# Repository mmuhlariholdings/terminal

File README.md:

<div align="center">

# Terminal 1

**A pocket Linux terminal with a real keyboard.**
Square 720 × 720 screen · BlackBerry Q20 keyboard and trackpad · Raspberry Pi CM4 · USB-C · carbon fibre back

[Website](https://mmuhlariholdings.github.io/terminal/) · [Product plan](system/plan/product-plan.md) · [3D model (Onshape)](https://cad.onshape.com/documents/8bfe7e43f7d7ec8135f9a829/w/29c38cad0998e4a6472b08e0/e/69201118ddf43601f28283ef) · [Contribute](CONTRIBUTING.md)

</div>

> [!IMPORTANT]
> **This project is vibe coded.** The plan, CAD, schematics, board layouts, firmware, Linux setup, docs and website are written
> largely by an AI coding assistant (Claude Code), directed and reviewed by humans. **Nothing has been built or tested on real
> hardware yet.** Treat every number as an estimate until a datasheet or a bench test confirms it. Items not yet verified are
> marked `CHECK` or *verify*. Checking them is one of the most useful contributions you can make. Why we work this way:
> [decision 0010](docs/decisions/0010-built-openly-with-an-ai-coding-assistant.md).

---

Terminal 1 does one job well: **working in a shell** on the go. SSH, `az login --use-device-code`, Claude Code, git, tmux,
everyday Linux. It boots straight into a full-screen terminal: no desktop, no browser, no notifications. Wi-Fi plus your
phone's hotspot covers connectivity.

It is a learning project first: KiCad, PCBs from JLCPCB and PCBWay, sourcing, 3D printing, carbon composites and Linux. We buy
proven modules where building them would teach little (the CM4 and the keyboard) and design our own boards around them.

## At a glance

| | |
|---|---|
| **Screen** | 4-inch 720 × 720 IPS, MIPI DSI: **90 × 45 characters** with an 8 × 16 font |
| **Keyboard** | BlackBerry Q20 replacement keyboard + trackpad; Ctrl / Esc / Tab / Fn above the keys; trackpad as arrow keys |
| **Computer** | Raspberry Pi Compute Module 4: 4 × Cortex-A72, 4 GB RAM, 32 GB eMMC, Wi-Fi 5, Bluetooth 5 |
| **Software** | Raspberry Pi OS Lite 64-bit · cage + foot · zsh · tmux · NetworkManager · Azure CLI · Node.js 22 · Claude Code |
| **Power** | 1S LiPo about 4,000–4,500 mAh, USB-C charging, runs while charging; about 4–6 h of terminal use (estimate) |
| **Size** | 84 × 150 × 19 mm, about 291 g (from the CAD model) |
| **Build** | Black aluminium mid-frame, carbon fibre back with a fibreglass radio window |
| **Our boards** | Keyboard and power board (RP2040, BQ25895, 5 V boost, MAX17048) · CM4 carrier board (4 layers, DSI, RTC) |

## Status

**Phase 0 (bench prototype) is next. First design pass done on 2026-11-16.**

| Area | State | Where |
|---|---|---|
| Plan | Converted to a living plan, decisions recorded | [`system/plan/`](system/plan/) · [`docs/decisions/`](docs/decisions/README.md) |
| 3D model | Full stack modelled in Onshape (FeatureScript), regenerates; fit check done | [`hardware/enclosure/`](hardware/enclosure/README.md) |
| Keyboard and power board | Pin map and circuit choices settled in the firmware; **schematic and layout not written yet** | [`hardware/keyboard-board/`](hardware/keyboard-board/README.md) |
| CM4 carrier board | Schematic ERC clean; layout DRC 0 violations; DSI and USB pairs still to route by hand | [`hardware/carrier-board/`](hardware/carrier-board/README.md) |
| Keyboard firmware | Written (Pico SDK + TinyUSB); host tests 5/5 pass; cross-compile runs in CI; not yet on hardware | [`firmware/keyboard-board/`](firmware/keyboard-board/README.md) |
| Linux | Installer, configs and status daemon written and unit tested; not yet run on a CM4 | [`linux/`](linux/README.md) |
| Website | Static launch page with the 3D model | [`website/`](website/README.md) |

## Roadmap

| Phase | What | Gate |
|---|---|---|
| **0 · Bench prototype** ← *we are here* | CM4 on its IO board, Q20 keyboard on a Pico, screen on the desk | SSH, `az login` and Claude Code from the bench keyboard |
| 1 · Keyboard and power board | Our RP2040 board from JLCPCB | Reliable typing, safe charging, clean shutdown from the power button |
| 2 · Carrier board | Our 4-layer CM4 carrier | Boots from the battery with screen and Wi-Fi |
| 3 · Enclosure | Printed shell → aluminium mid-frame → carbon back | Fits a jacket pocket, stays cool, Wi-Fi works with the back on |
| 4 · Daily driver | Battery tuning, disk encryption, key map refined | Two weeks without reaching for the laptop |
| 5 · Terminal 2 | Modem, bigger battery, optional CM5 | |

## Repository map

```
system/plan/          product-plan.md (the living plan) · interfaces.md (shared numbers) · the original PDF
docs/                 conventions.md · decisions/ (why things are the way they are) · media/ (renders)
hardware/enclosure/   terminal-1.fs (the Onshape model as code) · build sheet · .glb export
hardware/keyboard-board/   RP2040 keyboard and power board: generators, KiCad project, Gerbers, build sheet
hardware/carrier-board/    CM4 carrier: generators, KiCad project, routing notes, build sheet
firmware/keyboard-board/   RP2040 firmware (key map, trackpad, USB, power state machine) + host tests
linux/                install.sh, configs, terminal-1-statusd, pi-gen image stage
tools/                shared Python generators (KiCad schematic writer, board builder, checks)
website/              the launch page (static, GitHub Pages)
```

## Getting started

| You want to… | Start here |
|---|---|
| Understand the device | [Product plan](system/plan/product-plan.md), then [interfaces](system/plan/interfaces.md) |
| Look at the 3D model | [Onshape document](https://cad.onshape.com/documents/8bfe7e43f7d7ec8135f9a829/w/29c38cad0998e4a6472b08e0/e/69201118ddf43601f28283ef) and [`hardware/enclosure/`](hardware/enclosure/README.md) |
| Build the Phase 0 bench prototype | [`linux/README.md`](linux/README.md) and [`firmware/keyboard-board/README.md`](firmware/keyboard-board/) |
| Regenerate a schematic | `python3 hardware/<board>/electronics/generate_schematic.py --erc` (KiCad 10 installed) |
| Run the checks locally | `python3 tools/check_decisions.py` · `python3 -m unittest discover -s linux/status-daemon/tests` |
| Preview the website | `python3 -m http.server -d website/public 8000` → http://localhost:8000 |

Tools: git, Python 3, [KiCad 10](https://www.kicad.org/) (schematics, boards; its Python runs the board scripts), Java 21 (the
Freerouting autorouter), the [Pico SDK](https://github.com/raspberrypi/pico-sdk) and an Arm GCC toolchain (firmware), an
[Onshape](https://www.onshape.com/) account (free for public documents).

## Contributing

Everyone is welcome: electronics, CAD, firmware, Linux, docs, design, or simply **checking a datasheet against our files**.
Read [`CONTRIBUTING.md`](CONTRIBUTING.md), pick an issue labelled
[`good first issue`](https://github.com/mmuhlariholdings/terminal/labels/good%20first%20issue), and open a pull request.
Please follow the [Code of Conduct](CODE_OF_CONDUCT.md). Security issues: [`SECURITY.md`](SECURITY.md).

## Standing on shoulders

Beepy (SQFMI), Hackberry Pi, Solder Party's BBQ20KBD, ClockworkPi uConsole and MNT Pocket Reform showed the way; Raspberry Pi
publishes the CM4 IO board design we base our carrier on. Thank you.

## Licence

Hardware **CERN-OHL-S-2.0**, software **MIT**, documentation **CC BY-SA 4.0**. See [`LICENSE`](LICENSE). Terminal 1 is not
affiliated with Raspberry Pi Ltd or BlackBerry Ltd; their names are used only to describe the parts used.

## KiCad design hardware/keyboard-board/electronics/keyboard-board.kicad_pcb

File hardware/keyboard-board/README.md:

# Keyboard and power board

The 2-layer board behind the keyboard: RP2040 (keyboard, trackpad, USB device, power manager), BlackBerry Q20 keyboard and
trackpad connector, BQ25895 charger with power path, TPS61089 5.08 V boost for the CM4, MAX17048 gauge, USB-C, a TS3USB221
USB switch for service mode, power button, and the 24-way cable to the carrier board. 74 × 60 mm, Rev A.
Interfaces: [`system/plan/interfaces.md`](../../system/plan/interfaces.md) sections 3, 4, 6–8. Why: decisions 0004–0006.

## Status (2026-11-17)

STATUS_LINES

**Not ready to order.** The list of what must happen first is in [`build-sheet.md`](build-sheet.md) ("Before ordering").

## Where things are

| File | What |
|---|---|
| [`build-sheet.md`](build-sheet.md) | Design spec: inputs, outline, placement, parts and how sure each LCSC number is, checks, open items |
| [`electronics/generate_schematic.py`](electronics/generate_schematic.py) | The schematic, as a script (owns the RP2040 pin map) |
| [`electronics/parts.py`](electronics/parts.py) | LCSC numbers and footprints |
| [`electronics/pin-map.md`](electronics/pin-map.md) | RP2040 GPIOs, keyboard matrix, connector pinouts (generated) |
| [`electronics/netlist.md`](electronics/netlist.md) | Every net and part (generated) |
| [`electronics/circuit-notes.md`](electronics/circuit-notes.md) | Hand calculations: boost peak current, inductors, charger, LDO, battery life (estimates) |
| [`electronics/harness.md`](electronics/harness.md) | Cable and wires |
| [`electronics/generate_pcb.py`](electronics/generate_pcb.py) | The layout, as a script (placement, autorouting, DRC, renders, Gerbers, JLCPCB files) |
| `electronics/renders/`, `electronics/fabrication/` | Generated renders, Gerbers and JLCPCB BOM / placement files |
| [`../../firmware/keyboard-board/`](../../firmware/keyboard-board/) | The RP2040 firmware (its `src/board.h` must match `pin-map.md`; the schematic script checks it) |

## Rebuild

```sh
cd hardware/keyboard-board/electronics
python3 generate_schematic.py --erc        # schematic, net list, pin map, PDF; KiCad ERC must say 0 errors, 0 warnings
tools/fetch_tools.sh                       # once, from the repository root: Freerouting 2.0.1 (needs Java 21)
/Applications/KiCad/KiCad.app/Contents/Frameworks/Python.framework/Versions/3.9/bin/python3 generate_pcb.py --all
```

## Credits

The keyboard connector pinout, trackpad level shifting and matrix wiring follow Solder Party's
[BBQ20KBD](https://github.com/solderparty/bbq20kbd_hw) (CERN-OHL-1.2) and its firmware
[i2c_puppet](https://github.com/solderparty/i2c_puppet) (MIT). The RP2040 core circuit follows the Raspberry Pi Pico.

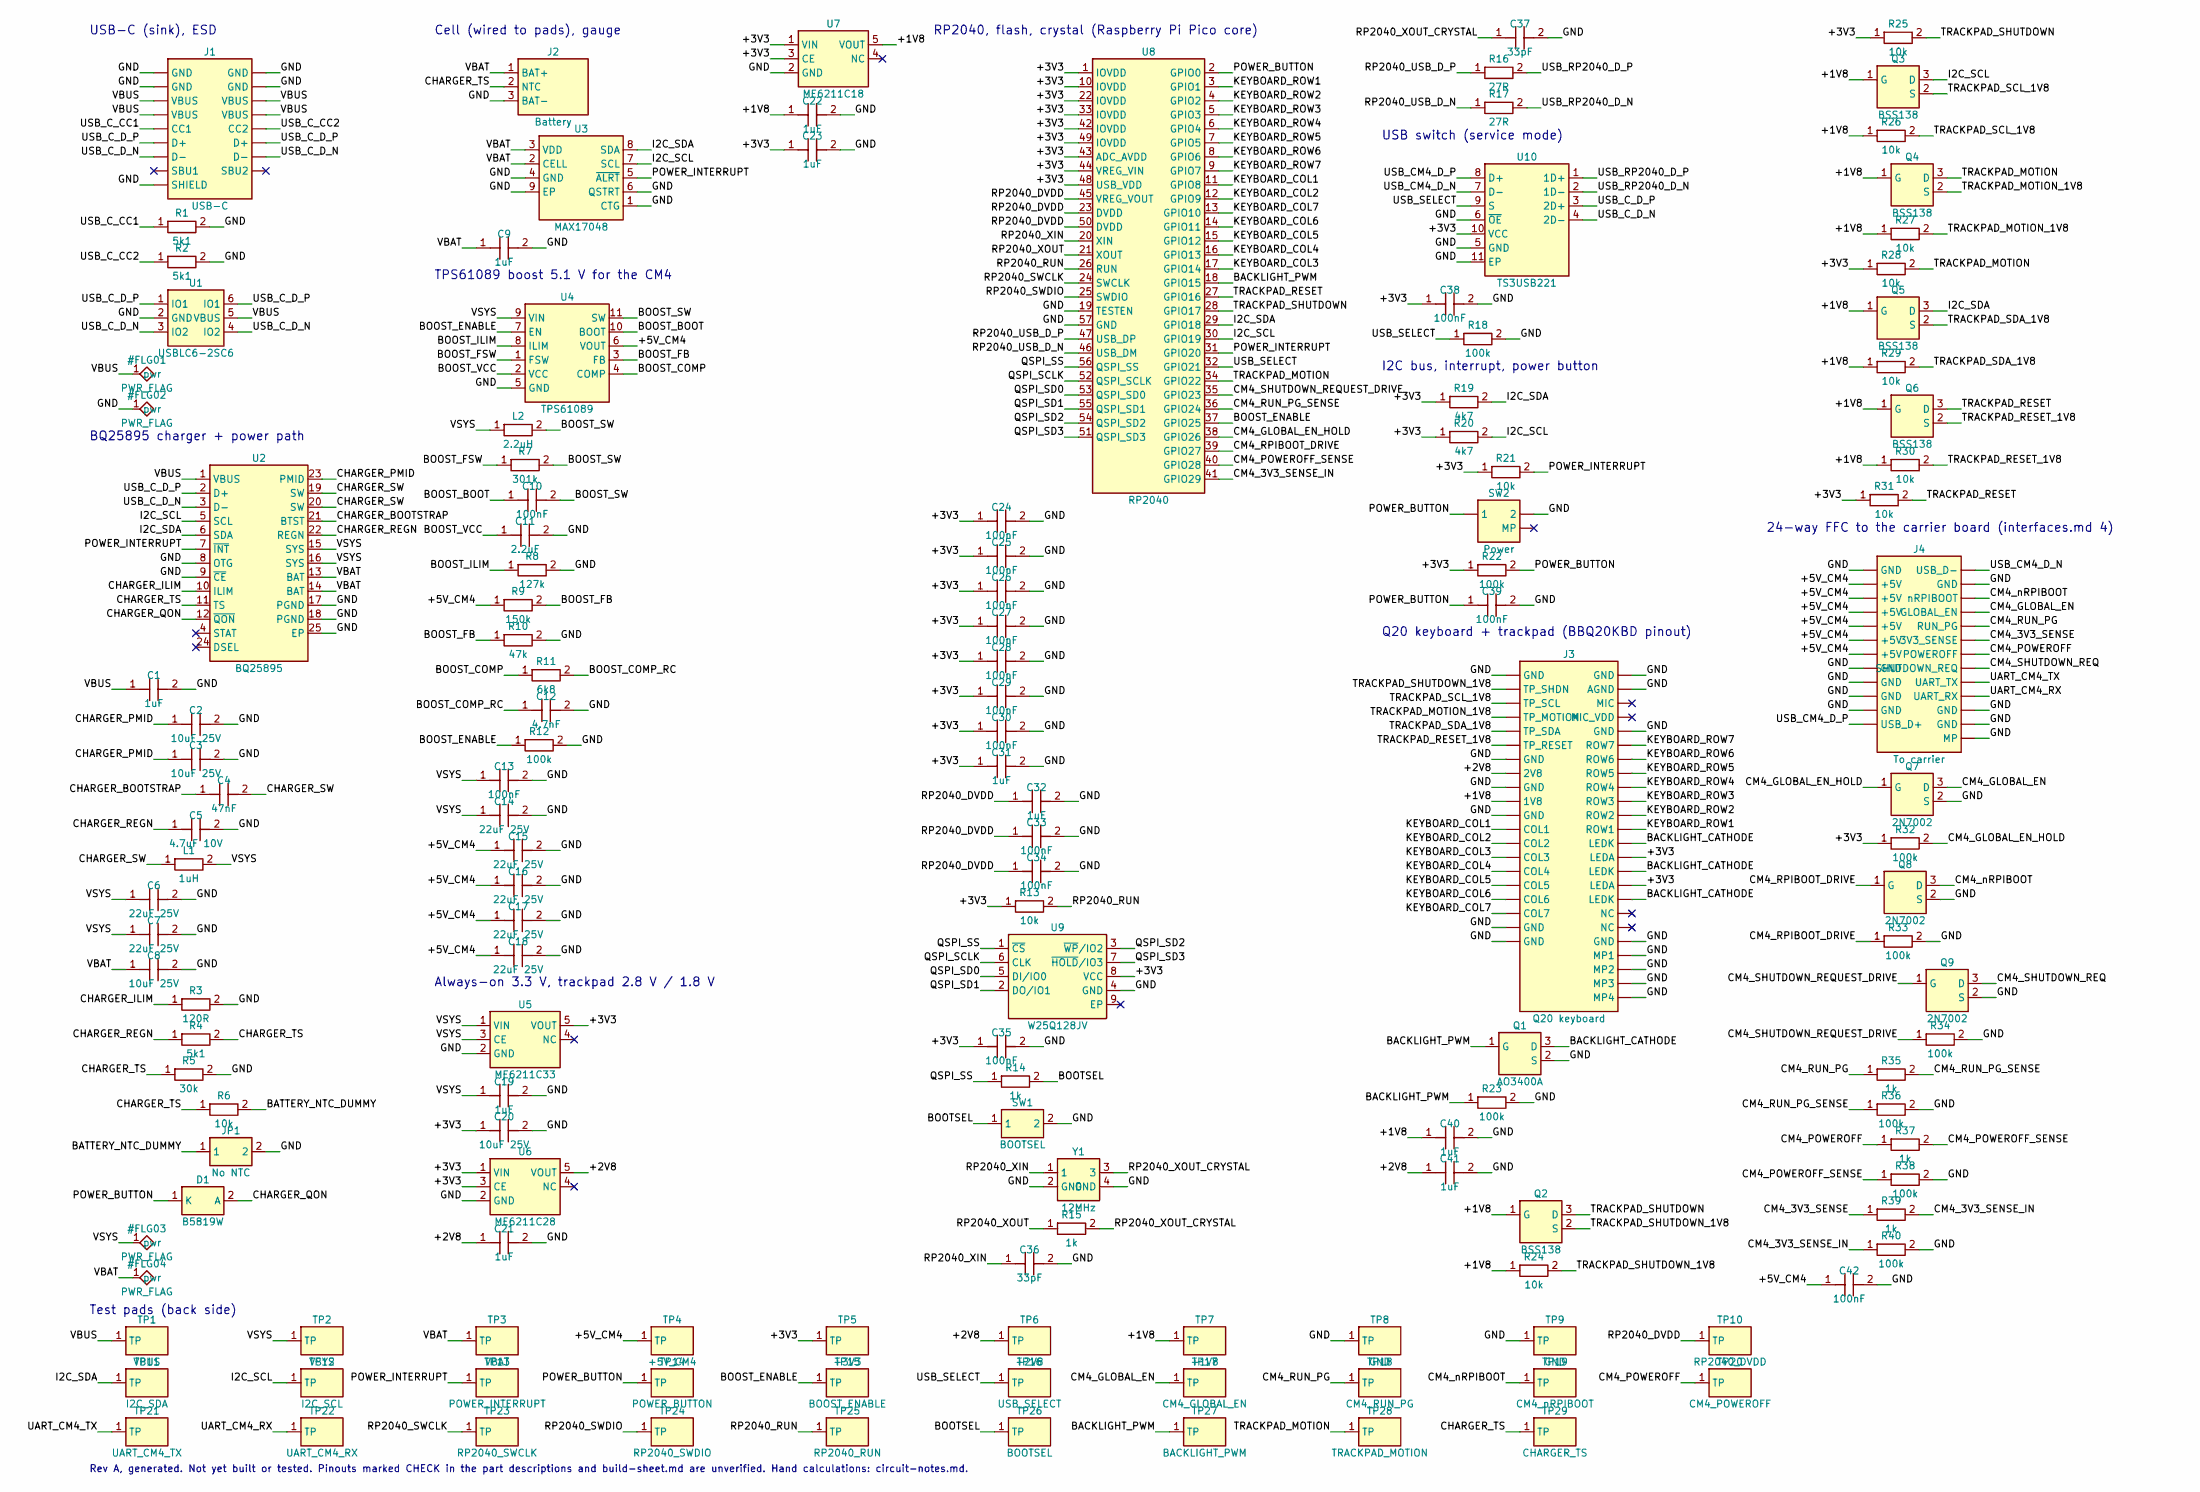
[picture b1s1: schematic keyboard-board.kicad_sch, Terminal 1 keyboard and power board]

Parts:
C1, C9, C19, C21, C22, C23, C31, C32, C40, C41: 1uF; C_0603_1608Metric; LCSC C15849
C2, C3, C8, C20: 10uF 25V; C_0805_2012Metric; LCSC C15850
C4: 47nF; C_0603_1608Metric
C5: 4.7uF 10V; C_0603_1608Metric
C6, C7, C14, C15, C16, C17, C18: 22uF 25V; C_1206_3216Metric; LCSC C12891
C10, C13, C24, C25, C26, C27, C28, C29, C30, C33, C34, C35, C38, C39, C42: 100nF; C_0603_1608Metric; LCSC C14663
C11: 2.2uF; C_0603_1608Metric
C12: 4.7nF; C_0603_1608Metric
C36, C37: 33pF; C_0603_1608Metric
D1: B5819W; D_SOD-123; LCSC C8598
J1: USB-C; USB_C_Receptacle_HRO_TYPE-C-31-M-12; LCSC C165948
J2: Battery; SolderWire-0.5sqmm_1x03_P4.6mm_D0.9mm_OD2.1mm
J3: Q20 keyboard; Hirose_BM20B-0.8-40DS-0.4V; LCSC C424543
J4: To carrier; Hirose_FH12-24S-0.5SH_1x24-1MP_P0.50mm_Horizontal; LCSC C202112
JP1: No NTC; SolderJumper-2_P1.3mm_Open_RoundedPad1.0x1.5mm
L1: 1uH; L_Changjiang_FXL0420; LCSC C167203
L2: 2.2uH; L_Changjiang_FXL0630; LCSC C167218
Q1: AO3400A; SOT-23; LCSC C20917
Q2, Q3, Q4, Q5, Q6: BSS138; SOT-23; LCSC C78284
Q7, Q8, Q9: 2N7002; SOT-23; LCSC C8545
R1, R2, R4: 5k1; R_0603_1608Metric; LCSC C23186
R3: 120R; R_0603_1608Metric
R5: 30k; R_0603_1608Metric
R6, R13, R21, R24, R25, R26, R27, R28, R29, R30, R31: 10k; R_0603_1608Metric; LCSC C25804
R7: 301k; R_0603_1608Metric
R8: 127k; R_0603_1608Metric
R9: 150k; R_0603_1608Metric
R10: 47k; R_0603_1608Metric
R11: 6k8; R_0603_1608Metric
R12, R18, R22, R23, R32, R33, R34, R36, R38, R40: 100k; R_0603_1608Metric; LCSC C25803
R14, R15, R35, R37, R39: 1k; R_0603_1608Metric; LCSC C21190
R16, R17: 27R; R_0603_1608Metric
R19, R20: 4k7; R_0603_1608Metric; LCSC C23162
SW1: BOOTSEL; SW_Push_1P1T_XKB_TS-1187A; LCSC C318884
SW2: Power; SW_Push_1P1T-MP_NO_Horizontal_Alps_SKRTLAE010; LCSC C110293
TP1: VBUS; TestPoint_Pad_D1.5mm
TP2: VSYS; TestPoint_Pad_D1.5mm
TP3: VBAT; TestPoint_Pad_D1.5mm
TP4: +5V_CM4; TestPoint_Pad_D1.5mm
TP5: +3V3; TestPoint_Pad_D1.5mm
TP6: +2V8; TestPoint_Pad_D1.5mm
TP7: +1V8; TestPoint_Pad_D1.5mm
TP8, TP9: GND; TestPoint_Pad_D1.5mm
TP10: RP2040_DVDD; TestPoint_Pad_D1.5mm
TP11: I2C_SDA; TestPoint_Pad_D1.5mm
TP12: I2C_SCL; TestPoint_Pad_D1.5mm
TP13: POWER_INTERRUPT; TestPoint_Pad_D1.5mm
TP14: POWER_BUTTON; TestPoint_Pad_D1.5mm
TP15: BOOST_ENABLE; TestPoint_Pad_D1.5mm
TP16: USB_SELECT; TestPoint_Pad_D1.5mm
TP17: CM4_GLOBAL_EN; TestPoint_Pad_D1.5mm
TP18: CM4_RUN_PG; TestPoint_Pad_D1.5mm
TP19: CM4_nRPIBOOT; TestPoint_Pad_D1.5mm
TP20: CM4_POWEROFF; TestPoint_Pad_D1.5mm
TP21: UART_CM4_TX; TestPoint_Pad_D1.5mm
TP22: UART_CM4_RX; TestPoint_Pad_D1.5mm
TP23: RP2040_SWCLK; TestPoint_Pad_D1.5mm
TP24: RP2040_SWDIO; TestPoint_Pad_D1.5mm
TP25: RP2040_RUN; TestPoint_Pad_D1.5mm
TP26: BOOTSEL; TestPoint_Pad_D1.5mm
TP27: BACKLIGHT_PWM; TestPoint_Pad_D1.5mm
TP28: TRACKPAD_MOTION; TestPoint_Pad_D1.5mm
TP29: CHARGER_TS; TestPoint_Pad_D1.5mm
U1: USBLC6-2SC6; SOT-23-6; LCSC C7519
U2: BQ25895; Texas_RTW_WQFN-24-1EP_4x4mm_P0.5mm_EP2.7x2.7mm; LCSC C80200
U3: MAX17048; TDFN-8-1EP_2x2mm_P0.5mm_EP0.8x1.2mm; LCSC C2682616
U4: TPS61089; Texas_VQFN-RNR0011A-11; LCSC C165129
U5: ME6211C33; SOT-23-5; LCSC C82942
U6: ME6211C28; SOT-23-5; LCSC C53099
U7: ME6211C18; SOT-23-5; LCSC C236671
U8: RP2040; QFN-56-1EP_7x7mm_P0.4mm_EP3.2x3.2mm; LCSC C2040
U9: W25Q128JV; WSON-8-1EP_6x5mm_P1.27mm_EP3.4x4.3mm; LCSC C190862
U10: TS3USB221; VSON-10-1EP_3x3mm_P0.5mm_EP1.65x2.4mm; LCSC C324071
Y1: 12MHz; Crystal_SMD_3225-4Pin_3.2x2.5mm; LCSC C9002

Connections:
/+1V8: C22.1, C40.1, J3.10 (1V8), Q2.1 (G), Q3.1 (G), Q4.1 (G), Q5.1 (G), Q6.1 (G), R24.1, R26.1, R27.1, R29.1, R30.1, TP7.1, U7.5 (VOUT)
/+2V8: C21.1, C41.1, J3.8 (2V8), TP6.1, U6.5 (VOUT)
/+3V3: C20.1, C23.1, C24.1, C25.1, C26.1, C27.1, C28.1, C29.1, C30.1, C31.1, C35.1, C38.1, J3.34 (LEDA), J3.36 (LEDA), R13.1, R19.1, R20.1, R21.1, R22.1, R25.1, R28.1, R31.1, R32.1, TP5.1, U5.5 (VOUT), U6.1 (VIN), U6.3 (CE), U7.1 (VIN), U7.3 (CE), U8.1 (IOVDD), U8.10 (IOVDD), U8.22 (IOVDD), U8.33 (IOVDD), U8.42 (IOVDD), U8.43 (ADC_AVDD), U8.44 (VREG_VIN), U8.48 (USB_VDD), U8.49 (IOVDD), U9.8 (VCC), U10.10 (VCC)
/+5V_CM4: C15.1, C16.1, C17.1, C18.1, C42.1, J4.2 (+5V), J4.3 (+5V), J4.4 (+5V), J4.5 (+5V), J4.6 (+5V), J4.7 (+5V), R9.1, TP4.1, U4.6 (VOUT)
/BACKLIGHT_CATHODE: J3.33 (LEDK), J3.35 (LEDK), J3.37 (LEDK), Q1.3 (D)
/BACKLIGHT_PWM: Q1.1 (G), R23.1, TP27.1, U8.18 (GPIO15)
/BATTERY_NTC_DUMMY: JP1.1, R6.2
/BOOST_BOOT: C10.1, U4.10 (BOOT)
/BOOST_COMP: R11.1, U4.4 (COMP)
/BOOST_COMP_RC: C12.1, R11.2
/BOOST_ENABLE: R12.1, TP15.1, U4.7 (EN), U8.37 (GPIO25)
/BOOST_FB: R9.2, R10.1, U4.3 (FB)
/BOOST_FSW: R7.1, U4.1 (FSW)
/BOOST_ILIM: R8.1, U4.8 (ILIM)
/BOOST_SW: C10.2, L2.2, R7.2, U4.11 (SW)
/BOOST_VCC: C11.1, U4.2 (VCC)
/BOOTSEL: R14.2, SW1.1, TP26.1
/CHARGER_BOOTSTRAP: C4.1, U2.21 (BTST)
/CHARGER_ILIM: R3.1, U2.10 (ILIM)
/CHARGER_PMID: C2.1, C3.1, U2.23 (PMID)
/CHARGER_QON: D1.2 (A), U2.12 (~QON)
/CHARGER_REGN: C5.1, R4.1, U2.22 (REGN)
/CHARGER_SW: C4.2, L1.1, U2.19 (SW), U2.20 (SW)
/CHARGER_TS: J2.2 (NTC), R4.2, R5.1, R6.1, TP29.1, U2.11 (TS)
/CM4_3V3_SENSE: J4.18 (3V3_SENSE), R39.1
/CM4_3V3_SENSE_IN: R39.2, R40.1, U8.41 (GPIO29)
/CM4_GLOBAL_EN: J4.16 (GLOBAL_EN), Q7.3 (D), TP17.1
/CM4_GLOBAL_EN_HOLD: Q7.1 (G), R32.2, U8.38 (GPIO26)
/CM4_POWEROFF: J4.19 (POWEROFF), R37.1, TP20.1
/CM4_POWEROFF_SENSE: R37.2, R38.1, U8.40 (GPIO28)
/CM4_RPIBOOT_DRIVE: Q8.1 (G), R33.1, U8.39 (GPIO27)
/CM4_RUN_PG: J4.17 (RUN_PG), R35.1, TP18.1
/CM4_RUN_PG_SENSE: R35.2, R36.1, U8.36 (GPIO24)
/CM4_SHUTDOWN_REQ: J4.20 (SHUTDOWN_REQ), Q9.3 (D)
/CM4_SHUTDOWN_REQUEST_DRIVE: Q9.1 (G), R34.1, U8.35 (GPIO23)
/CM4_nRPIBOOT: J4.15 (nRPIBOOT), Q8.3 (D), TP19.1
/GND: C1.2, C2.2, C3.2, C5.2, C6.2, C7.2, C8.2, C9.2, C11.2, C12.2, C13.2, C14.2, C15.2, C16.2, C17.2, C18.2, C19.2, C20.2, C21.2, C22.2, C23.2, C24.2, C25.2, C26.2, C27.2, C28.2, C29.2, C30.2, C31.2, C32.2, C33.2, C34.2, C35.2, C36.2, C37.2, C38.2, C39.2, C40.2, C41.2, C42.2, J1.A1 (GND), J1.A12 (GND), J1.B1 (GND), J1.B12 (GND), J1.SH (SHIELD), J2.3 (BAT-), J3.1 (GND), J3.7 (GND), J3.9 (GND), J3.11 (GND), J3.19 (GND), J3.20 (GND), J3.21 (GND), J3.22 (AGND), J3.25 (GND), J3.40 (GND), J3.MP1, J3.MP2, J3.MP3, J3.MP4, J4.1 (GND), J4.8 (GND), J4.9 (GND), J4.10 (GND), J4.11 (GND), J4.14 (GND), J4.23 (GND), J4.24 (GND), J4.MP, JP1.2, Q1.2 (S), Q7.2 (S), Q8.2 (S), Q9.2 (S), R1.2, R2.2, R3.2, R5.2, R8.2, R10.2, R12.2, R18.2, R23.2, R33.2, R34.2, R36.2, R38.2, R40.2, SW1.2, SW2.2, TP8.1, TP9.1, U1.2 (GND), U2.8 (OTG), U2.9 (~CE), U2.17 (PGND), U2.18 (PGND), U2.25 (EP), U3.1 (CTG), U3.4 (GND), U3.6 (QSTRT), U3.9 (EP), U4.5 (GND), U5.2 (GND), U6.2 (GND), U7.2 (GND), U8.19 (TESTEN), U8.57 (GND), U9.4 (GND), U10.5 (GND), U10.6 (~OE), U10.11 (EP), Y1.2 (GND), Y1.4 (GND)
/I2C_SCL: Q3.3 (D), R20.2, TP12.1, U2.5 (SCL), U3.7 (SCL), U8.30 (GPIO19)
/I2C_SDA: Q5.3 (D), R19.2, TP11.1, U2.6 (SDA), U3.8 (SDA), U8.29 (GPIO18)
/KEYBOARD_COL1: J3.12 (COL1), U8.11 (GPIO8)
/KEYBOARD_COL2: J3.13 (COL2), U8.12 (GPIO9)
/KEYBOARD_COL3: J3.14 (COL3), U8.17 (GPIO14)
/KEYBOARD_COL4: J3.15 (COL4), U8.16 (GPIO13)
/KEYBOARD_COL5: J3.16 (COL5), U8.15 (GPIO12)
/KEYBOARD_COL6: J3.17 (COL6), U8.14 (GPIO11)
/KEYBOARD_COL7: J3.18 (COL7), U8.13 (GPIO10)
/KEYBOARD_ROW1: J3.32 (ROW1), U8.3 (GPIO1)
/KEYBOARD_ROW2: J3.31 (ROW2), U8.4 (GPIO2)
/KEYBOARD_ROW3: J3.30 (ROW3), U8.5 (GPIO3)
/KEYBOARD_ROW4: J3.29 (ROW4), U8.6 (GPIO4)
/KEYBOARD_ROW5: J3.28 (ROW5), U8.7 (GPIO5)
/KEYBOARD_ROW6: J3.27 (ROW6), U8.8 (GPIO6)
/KEYBOARD_ROW7: J3.26 (ROW7), U8.9 (GPIO7)
/POWER_BUTTON: C39.1, D1.1 (K), R22.2, SW2.1, TP14.1, U8.2 (GPIO0)
/POWER_INTERRUPT: R21.2, TP13.1, U2.7 (~INT), U3.5 (~ALRT), U8.31 (GPIO20)
/QSPI_SCLK: U8.52 (QSPI_SCLK), U9.6 (CLK)
/QSPI_SD0: U8.53 (QSPI_SD0), U9.5 (DI/IO0)
/QSPI_SD1: U8.55 (QSPI_SD1), U9.2 (DO/IO1)
/QSPI_SD2: U8.54 (QSPI_SD2), U9.3 (~WP/IO2)
/QSPI_SD3: U8.51 (QSPI_SD3), U9.7 (~HOLD/IO3)
/QSPI_SS: R14.1, U8.56 (QSPI_SS), U9.1 (~CS)
/RP2040_DVDD: C32.1, C33.1, C34.1, TP10.1, U8.23 (DVDD), U8.45 (VREG_VOUT), U8.50 (DVDD)
/RP2040_RUN: R13.2, TP25.1, U8.26 (RUN)
/RP2040_SWCLK: TP23.1, U8.24 (SWCLK)
/RP2040_SWDIO: TP24.1, U8.25 (SWDIO)
/RP2040_USB_D_N: R17.1, U8.46 (USB_DM)
/RP2040_USB_D_P: R16.1, U8.47 (USB_DP)
/RP2040_XIN: C36.1, U8.20 (XIN), Y1.1
/RP2040_XOUT: R15.1, U8.21 (XOUT)
/RP2040_XOUT_CRYSTAL: C37.1, R15.2, Y1.3
/TRACKPAD_MOTION: Q4.3 (D), R28.2, TP28.1, U8.34 (GPIO22)
/TRACKPAD_MOTION_1V8: J3.4 (TP_MOTION), Q4.2 (S), R27.2
/TRACKPAD_RESET: Q6.3 (D), R31.2, U8.27 (GPIO16)
/TRACKPAD_RESET_1V8: J3.6 (TP_RESET), Q6.2 (S), R30.2
/TRACKPAD_SCL_1V8: J3.3 (TP_SCL), Q3.2 (S), R26.2
/TRACKPAD_SDA_1V8: J3.5 (TP_SDA), Q5.2 (S), R29.2
/TRACKPAD_SHUTDOWN: Q2.3 (D), R25.2, U8.28 (GPIO17)
/TRACKPAD_SHUTDOWN_1V8: J3.2 (TP_SHDN), Q2.2 (S), R24.2
/UART_CM4_RX: J4.22 (UART_RX), TP22.1
/UART_CM4_TX: J4.21 (UART_TX), TP21.1
/USB_CM4_D_N: J4.13 (USB_D-), U10.7 (D-)
/USB_CM4_D_P: J4.12 (USB_D+), U10.8 (D+)
/USB_C_CC1: J1.A5 (CC1), R1.1
/USB_C_CC2: J1.B5 (CC2), R2.1
/USB_C_D_N: J1.A7 (D-), J1.B7 (D-), U1.3 (IO2), U1.4 (IO2), U2.3 (D-), U10.4 (2D-)
/USB_C_D_P: J1.A6 (D+), J1.B6 (D+), U1.1 (IO1), U1.6 (IO1), U2.2 (D+), U10.3 (2D+)
/USB_RP2040_D_N: R17.2, U10.2 (1D-)
/USB_RP2040_D_P: R16.2, U10.1 (1D+)
/USB_SELECT: R18.1, TP16.1, U8.32 (GPIO21), U10.9 (S)
/VBAT: C8.1, C9.1, J2.1 (BAT+), TP3.1, U2.13 (BAT), U2.14 (BAT), U3.2 (CELL), U3.3 (VDD)
/VBUS: C1.1, J1.A4 (VBUS), J1.A9 (VBUS), J1.B4 (VBUS), J1.B9 (VBUS), TP1.1, U1.5 (VBUS), U2.1 (VBUS)
/VSYS: C6.1, C7.1, C13.1, C14.1, C19.1, L1.2, L2.1, TP2.1, U2.15 (SYS), U2.16 (SYS), U4.9 (VIN), U5.1 (VIN), U5.3 (CE)

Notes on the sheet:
USB-C (sink), ESD
BQ25895 charger + power path
Cell (wired to pads), gauge
TPS61089 boost 5.1 V for the CM4
Always-on 3.3 V, trackpad 2.8 V / 1.8 V
RP2040, flash, crystal (Raspberry Pi Pico core)
USB switch (service mode)
I2C bus, interrupt, power button
Q20 keyboard + trackpad (BBQ20KBD pinout)
24-way FFC to the carrier board (interfaces.md 4)
Test pads (back side)
Rev A, generated. Not yet built or tested. Pinouts marked CHECK in the part descriptions and build-sheet.md are unverified. Hand calculations: circuit-notes.md.

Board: 2 copper layers, 145 parts (140 on the bottom side), 92 nets, no tracks yet.

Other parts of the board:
H1, H2, H3, H4: M2; MountingHole_2.2mm_M2

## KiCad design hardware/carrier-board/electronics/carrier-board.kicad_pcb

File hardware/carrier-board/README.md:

# CM4 carrier board

The 4-layer board behind the screen: Raspberry Pi CM4 on two Hirose DF40 connectors, the 22-pin DSI display connector (Pi
standard, as the CM4 IO board's DISP1), a PCF85063A real-time clock with a CR2032, status LEDs, serial console pads, and the
24-way cable to the keyboard board. 74 × 72 mm, Rev A. Design spec: [`build-sheet.md`](build-sheet.md).

## Status (2026-11-17)

| Check | Result |
|---|---|
| Schematic | Generated; **KiCad ERC 0 errors, 0 warnings** (32 parts, 45 nets); all 200 CM4 pins accounted for in [`electronics/pin-map.md`](electronics/pin-map.md) |
| Layout | Placed and autorouted except the high-speed pairs; **DRC 0 violations, 16 unconnected pads** (DSI1: 10, USB: 6) |
| Ready to order? | **No.** The DSI and USB pairs must be routed by hand: [`electronics/routing-notes.md`](electronics/routing-notes.md). Gerbers are in `electronics/fabrication/` marked **not for order** |
| Impedance | Estimated widths for JLCPCB JLC04161H-7628 in [`electronics/circuit-notes.md`](electronics/circuit-notes.md); confirm with JLCPCB's calculator |

## Regenerate

```sh
cd hardware/carrier-board/electronics
python3 generate_schematic.py --erc                     # schematic, ERC, PDF, netlist.md, pin-map.md
tools/fetch_tools.sh                                    # once, from the repository root: Freerouting
/Applications/KiCad/KiCad.app/Contents/Frameworks/Python.framework/Versions/3.9/bin/python3 generate_pcb.py --all
```

`generate_pcb.py` checks each of the CM4's 200 pads against the CM4 IO board footprint geometry and stops if any is off by more
than 0.01 mm. Its four-layer helpers are in `board_four_layer.py`; `estimate_impedance.py` reproduces the impedance table.

## Credits

Based on Raspberry Pi's CM4 IO board design (CM4IOv5): RTC circuit, status LEDs, DISP1 pinout and CM4 footprint geometry.
Raspberry Pi publishes those files for reuse in customers' designs; check their current terms before redistributing copies.

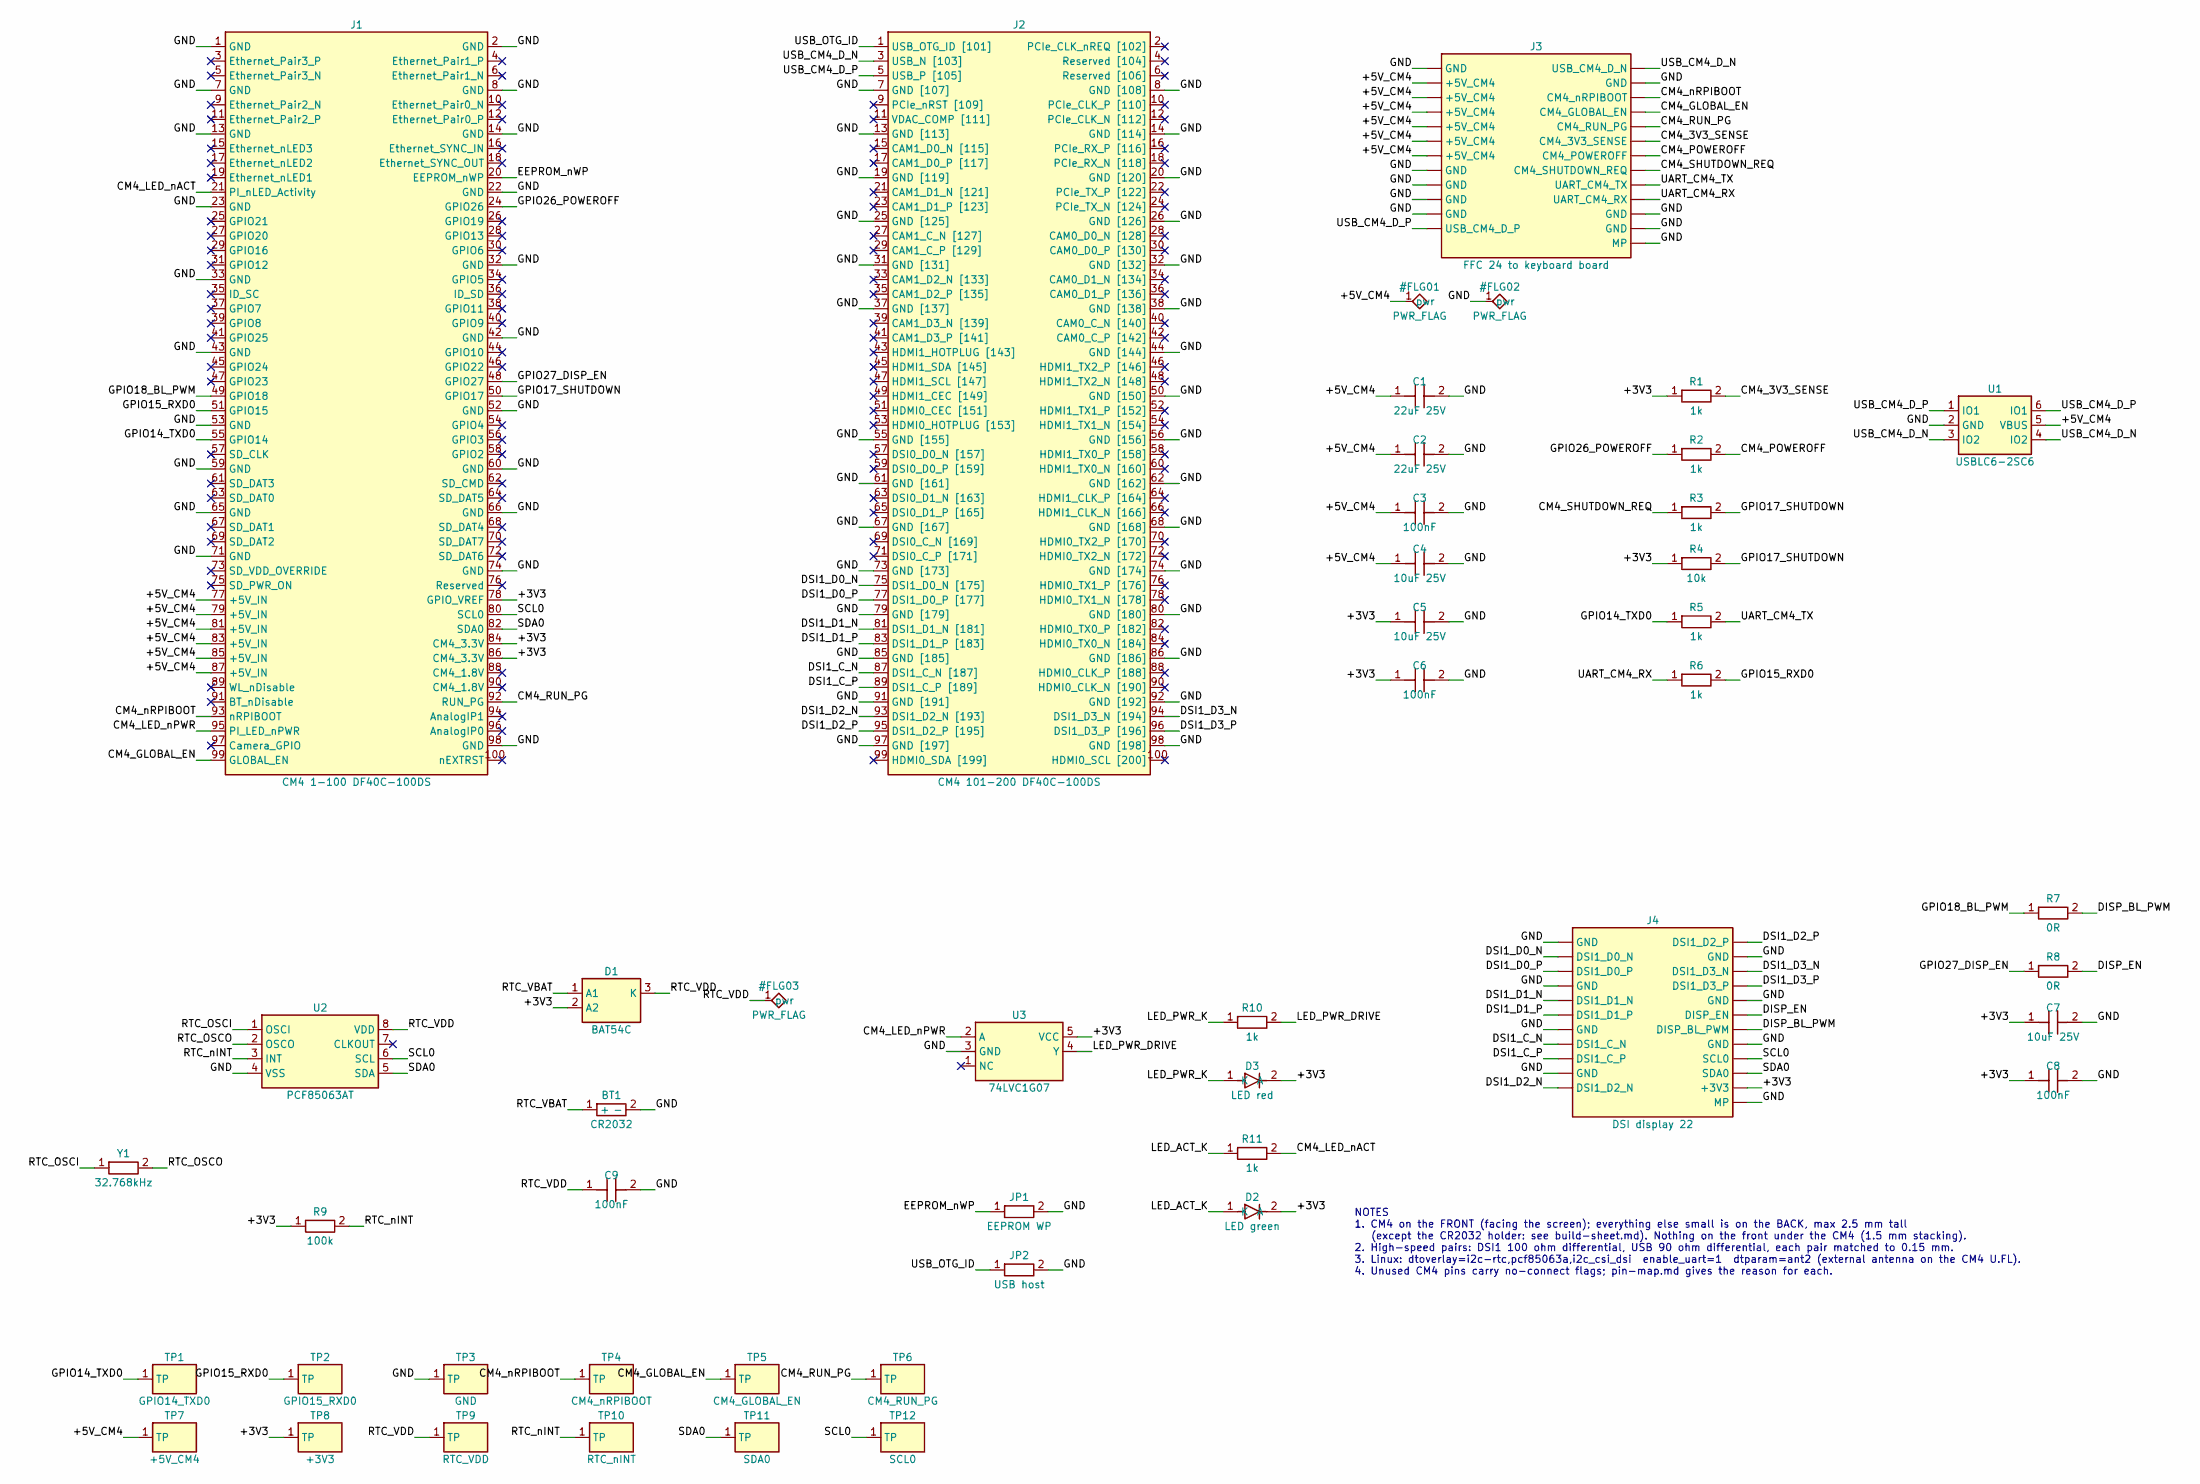
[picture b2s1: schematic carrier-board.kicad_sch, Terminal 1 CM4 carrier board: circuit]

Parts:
BT1: CR2032; BatteryHolder_Keystone_3034_1x20mm; LCSC CHECK
C1, C2: 22uF 25V; C_1206_3216Metric; LCSC C12891
C3, C6, C8, C9: 100nF; C_0603_1608Metric; LCSC C14663
C4, C5, C7: 10uF 25V; C_0805_2012Metric; LCSC C15850
D1: BAT54C; SOT-23; LCSC CHECK
D2: LED green; LED_0603_1608Metric; LCSC C72043
D3: LED red; LED_0603_1608Metric; LCSC C2286
J1: CM4 1-100 DF40C-100DS; Hirose_DF40C-100DS-0.4V_2x50_P0.4mm; LCSC CHECK
J2: CM4 101-200 DF40C-100DS; Hirose_DF40C-100DS-0.4V_2x50_P0.4mm; LCSC CHECK
J3: FFC 24 to keyboard board; Hirose_FH12-24S-0.5SH_1x24-1MP_P0.50mm_Horizontal; LCSC CHECK
J4: DSI display 22; Hirose_FH12-22S-0.5SH_1x22-1MP_P0.50mm_Horizontal; LCSC CHECK
JP1: EEPROM WP; SolderJumper-2_P1.3mm_Open_RoundedPad1.0x1.5mm
JP2: USB host; SolderJumper-2_P1.3mm_Open_RoundedPad1.0x1.5mm
R1, R2, R3, R5, R6, R10, R11: 1k; R_0603_1608Metric; LCSC C21190
R4: 10k; R_0603_1608Metric; LCSC C25804
R7, R8: 0R; R_0603_1608Metric; LCSC C21189
R9: 100k; R_0603_1608Metric; LCSC C25803
TP1: GPIO14_TXD0; TestPoint_Pad_D1.5mm
TP2: GPIO15_RXD0; TestPoint_Pad_D1.5mm
TP3: GND; TestPoint_Pad_D1.5mm
TP4: CM4_nRPIBOOT; TestPoint_Pad_D1.5mm
TP5: CM4_GLOBAL_EN; TestPoint_Pad_D1.5mm
TP6: CM4_RUN_PG; TestPoint_Pad_D1.5mm
TP7: +5V_CM4; TestPoint_Pad_D1.5mm
TP8: +3V3; TestPoint_Pad_D1.5mm
TP9: RTC_VDD; TestPoint_Pad_D1.5mm
TP10: RTC_nINT; TestPoint_Pad_D1.5mm
TP11: SDA0; TestPoint_Pad_D1.5mm
TP12: SCL0; TestPoint_Pad_D1.5mm
U1: USBLC6-2SC6; SOT-23-6; LCSC C7519
U2: PCF85063AT; SOIC-8_3.9x4.9mm_P1.27mm; LCSC CHECK
U3: 74LVC1G07; SOT-353_SC-70-5; LCSC CHECK
Y1: 32.768kHz; Crystal_SMD_3215-2Pin_3.2x1.5mm; LCSC CHECK

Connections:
/+3V3: C5.1, C6.1, C7.1, C8.1, D1.2 (A2), D2.2 (A), D3.2 (A), J1.78 (GPIO_VREF), J1.84 (CM4_3.3V), J1.86 (CM4_3.3V), J4.22 (+3V3), R1.1, R4.1, R9.1, TP8.1, U3.5 (VCC)
/+5V_CM4: C1.1, C2.1, C3.1, C4.1, J1.77 (+5V_IN), J1.79 (+5V_IN), J1.81 (+5V_IN), J1.83 (+5V_IN), J1.85 (+5V_IN), J1.87 (+5V_IN), J3.2 (+5V_CM4), J3.3 (+5V_CM4), J3.4 (+5V_CM4), J3.5 (+5V_CM4), J3.6 (+5V_CM4), J3.7 (+5V_CM4), TP7.1, U1.5 (VBUS)
/CM4_3V3_SENSE: J3.18 (CM4_3V3_SENSE), R1.2
/CM4_GLOBAL_EN: J1.99 (GLOBAL_EN), J3.16 (CM4_GLOBAL_EN), TP5.1
/CM4_LED_nACT: J1.21 (PI_nLED_Activity), R11.2
/CM4_LED_nPWR: J1.95 (PI_LED_nPWR), U3.2 (A)
/CM4_POWEROFF: J3.19 (CM4_POWEROFF), R2.2
/CM4_RUN_PG: J1.92 (RUN_PG), J3.17 (CM4_RUN_PG), TP6.1
/CM4_SHUTDOWN_REQ: J3.20 (CM4_SHUTDOWN_REQ), R3.1
/CM4_nRPIBOOT: J1.93 (nRPIBOOT), J3.15 (CM4_nRPIBOOT), TP4.1
/DISP_BL_PWM: J4.18 (DISP_BL_PWM), R7.2
/DISP_EN: J4.17 (DISP_EN), R8.2
/DSI1_C_N: J2.87 (DSI1_C_N [187]), J4.8 (DSI1_C_N)
/DSI1_C_P: J2.89 (DSI1_C_P [189]), J4.9 (DSI1_C_P)
/DSI1_D0_N: J2.75 (DSI1_D0_N [175]), J4.2 (DSI1_D0_N)
/DSI1_D0_P: J2.77 (DSI1_D0_P [177]), J4.3 (DSI1_D0_P)
/DSI1_D1_N: J2.81 (DSI1_D1_N [181]), J4.5 (DSI1_D1_N)
/DSI1_D1_P: J2.83 (DSI1_D1_P [183]), J4.6 (DSI1_D1_P)
/DSI1_D2_N: J2.93 (DSI1_D2_N [193]), J4.11 (DSI1_D2_N)
/DSI1_D2_P: J2.95 (DSI1_D2_P [195]), J4.12 (DSI1_D2_P)
/DSI1_D3_N: J2.94 (DSI1_D3_N [194]), J4.14 (DSI1_D3_N)
/DSI1_D3_P: J2.96 (DSI1_D3_P [196]), J4.15 (DSI1_D3_P)
/EEPROM_nWP: J1.20 (EEPROM_nWP), JP1.1
/GND: BT1.2 (-), C1.2, C2.2, C3.2, C4.2, C5.2, C6.2, C7.2, C8.2, C9.2, J1.1 (GND), J1.2 (GND), J1.7 (GND), J1.8 (GND), J1.13 (GND), J1.14 (GND), J1.22 (GND), J1.23 (GND), J1.32 (GND), J1.33 (GND), J1.42 (GND), J1.43 (GND), J1.52 (GND), J1.53 (GND), J1.59 (GND), J1.60 (GND), J1.65 (GND), J1.66 (GND), J1.71 (GND), J1.74 (GND), J1.98 (GND), J2.7 (GND [107]), J2.8 (GND [108]), J2.13 (GND [113]), J2.14 (GND [114]), J2.19 (GND [119]), J2.20 (GND [120]), J2.25 (GND [125]), J2.26 (GND [126]), J2.31 (GND [131]), J2.32 (GND [132]), J2.37 (GND [137]), J2.38 (GND [138]), J2.44 (GND [144]), J2.50 (GND [150]), J2.55 (GND [155]), J2.56 (GND [156]), J2.61 (GND [161]), J2.62 (GND [162]), J2.67 (GND [167]), J2.68 (GND [168]), J2.73 (GND [173]), J2.74 (GND [174]), J2.79 (GND [179]), J2.80 (GND [180]), J2.85 (GND [185]), J2.86 (GND [186]), J2.91 (GND [191]), J2.92 (GND [192]), J2.97 (GND [197]), J2.98 (GND [198]), J3.1 (GND), J3.8 (GND), J3.9 (GND), J3.10 (GND), J3.11 (GND), J3.14 (GND), J3.23 (GND), J3.24 (GND), J3.MP, J4.1 (GND), J4.4 (GND), J4.7 (GND), J4.10 (GND), J4.13 (GND), J4.16 (GND), J4.19 (GND), J4.MP, JP1.2, JP2.2, TP3.1, U1.2 (GND), U2.4 (VSS), U3.3 (GND)
/GPIO14_TXD0: J1.55 (GPIO14), R5.1, TP1.1
/GPIO15_RXD0: J1.51 (GPIO15), R6.2, TP2.1
/GPIO17_SHUTDOWN: J1.50 (GPIO17), R3.2, R4.2
/GPIO18_BL_PWM: J1.49 (GPIO18), R7.1
/GPIO26_POWEROFF: J1.24 (GPIO26), R2.1
/GPIO27_DISP_EN: J1.48 (GPIO27), R8.1
/LED_ACT_K: D2.1 (K), R11.1
/LED_PWR_DRIVE: R10.2, U3.4 (Y)
/LED_PWR_K: D3.1 (K), R10.1
/RTC_OSCI: U2.1 (OSCI), Y1.1
/RTC_OSCO: U2.2 (OSCO), Y1.2
/RTC_VBAT: BT1.1 (+), D1.1 (A1)
/RTC_VDD: C9.1, D1.3 (K), TP9.1, U2.8 (VDD)
/RTC_nINT: R9.2, TP10.1, U2.3 (INT)
/SCL0: J1.80 (SCL0), J4.20 (SCL0), TP12.1, U2.6 (SCL)
/SDA0: J1.82 (SDA0), J4.21 (SDA0), TP11.1, U2.5 (SDA)
/UART_CM4_RX: J3.22 (UART_CM4_RX), R6.1
/UART_CM4_TX: J3.21 (UART_CM4_TX), R5.2
/USB_CM4_D_N: J2.3 (USB_N [103]), J3.13 (USB_CM4_D_N), U1.3 (IO2), U1.4 (IO2)
/USB_CM4_D_P: J2.5 (USB_P [105]), J3.12 (USB_CM4_D_P), U1.1 (IO1), U1.6 (IO1)
/USB_OTG_ID: J2.1 (USB_OTG_ID [101]), JP2.1

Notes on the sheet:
NOTES 1. CM4 on the FRONT (facing the screen); everything else small is on the BACK, max 2.5 mm tall (except the CR2032 holder: see build-sheet.md). Nothing on the front under the CM4 (1.5 mm stacking). 2. High-speed pairs: DSI1 100 ohm differential, USB 90 ohm differential, each pair matched to 0.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

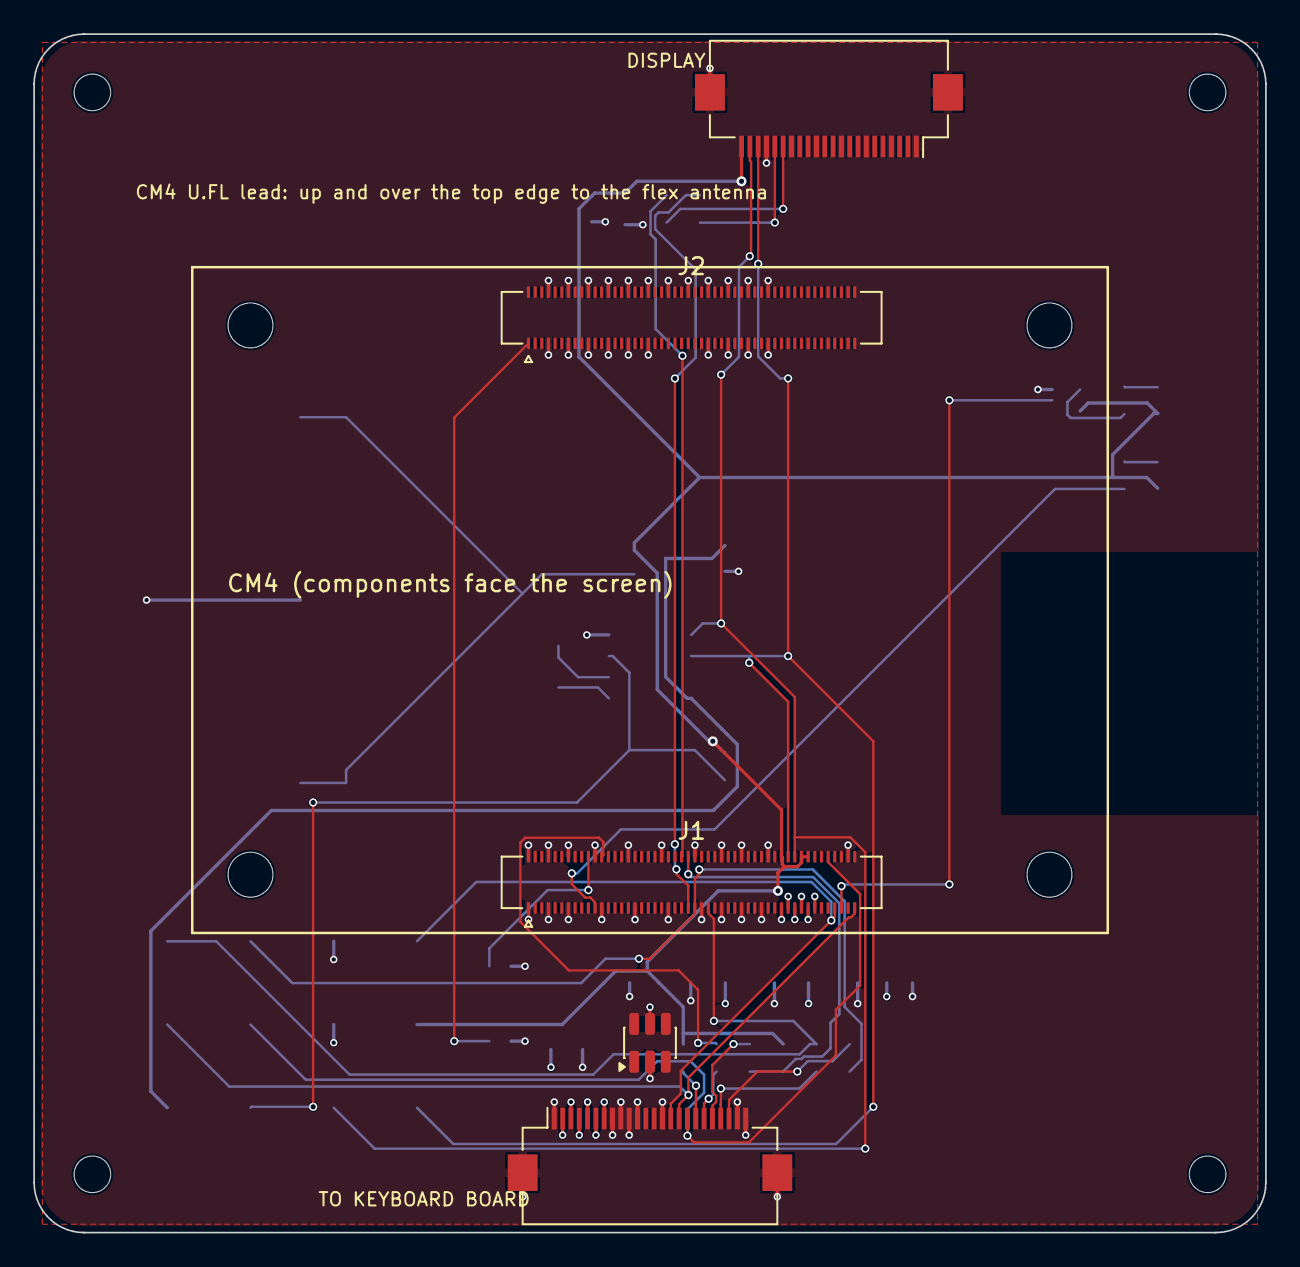
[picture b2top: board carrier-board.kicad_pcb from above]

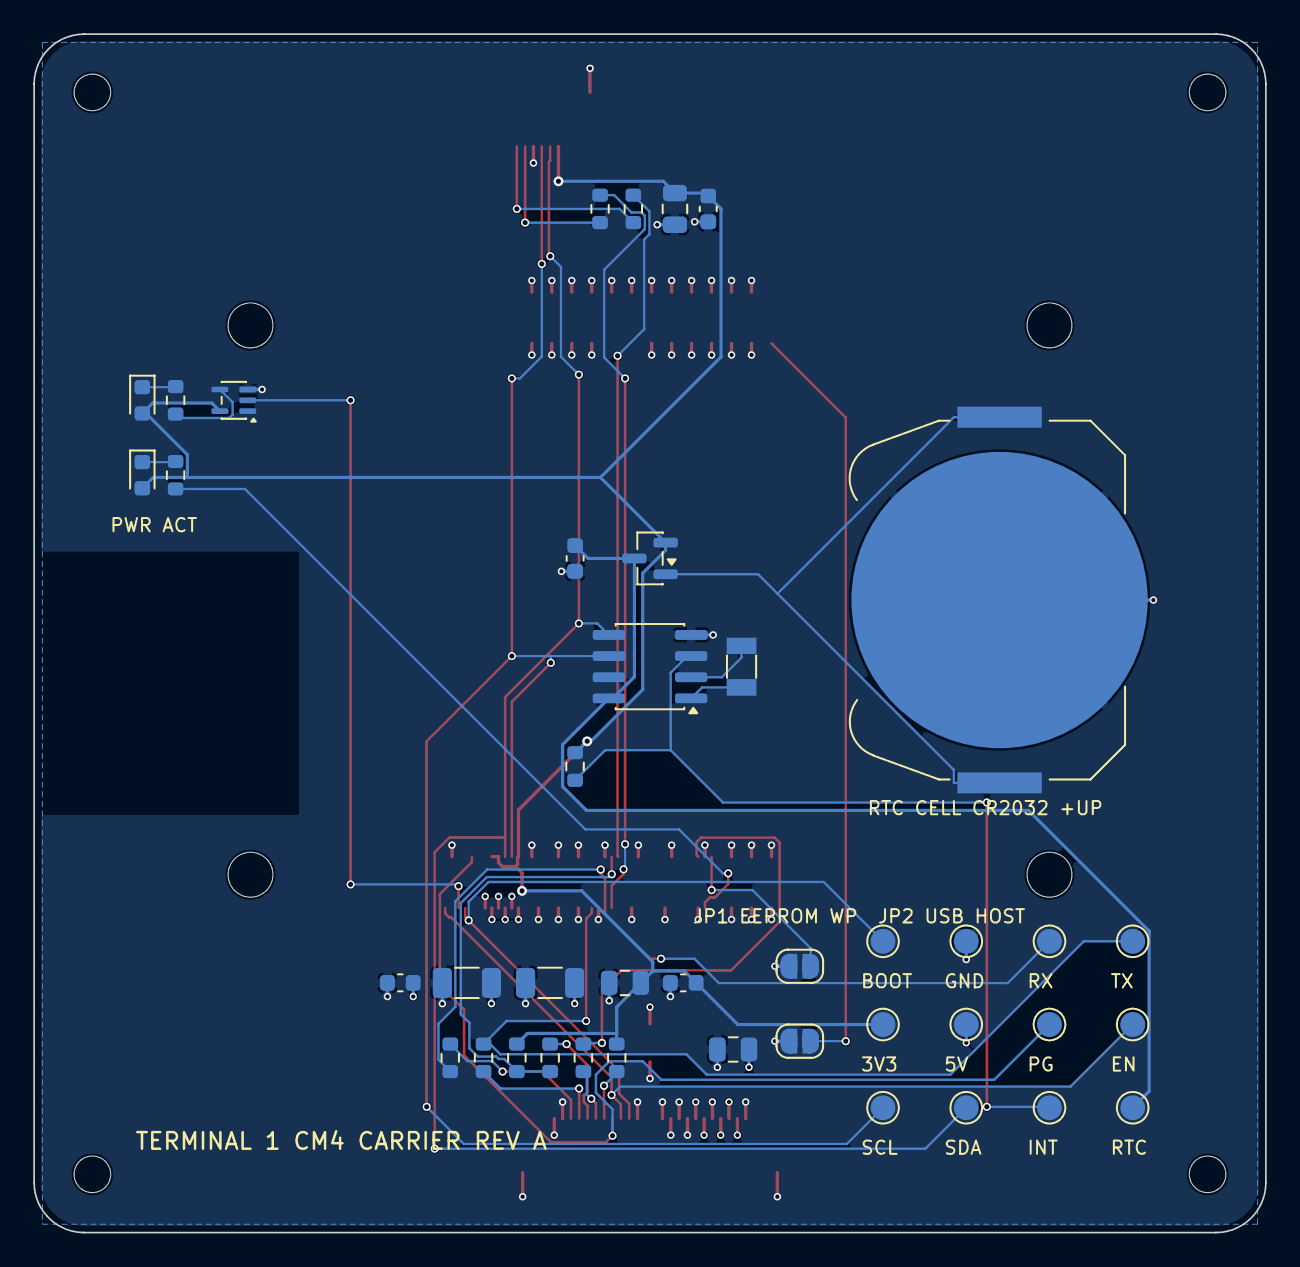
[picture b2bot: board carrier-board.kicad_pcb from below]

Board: 4 copper layers, 74.0 x 72.0 mm, 54 parts (41 on the bottom side), 45 nets.

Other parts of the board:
H1, H2, H3, H4: M2; MountingHole_2.2mm_M2
H5, H6, H7, H8: CM4 M2.5; MountingHole_2.7mm_M2.5

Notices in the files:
hardware/keyboard-board/electronics/keyboard-board.kicad_pcb:
github.com terminal-1 (CERN-OHL-S-2.0)
hardware/keyboard-board/electronics/keyboard-board.kicad_sch:
RP2040 scans the Q20 keyboard + trackpad (BBQ20KBD design, Solder Party, CERN-OHL-1.2) and owns power
parts and their libraries:
Hirose BM20B(0.8)-40DS-0.4V(51) 40-pin 0.4 mm receptacle for the BlackBerry Q20 keyboard flex. Pad geometry from the BBQ20KBD board (Solder Party, CERN-OHL-1.2). CHECK against the Hirose drawing. Generated by hardware/keyboard-board/electronics/keyboard_connector_footprint.py
